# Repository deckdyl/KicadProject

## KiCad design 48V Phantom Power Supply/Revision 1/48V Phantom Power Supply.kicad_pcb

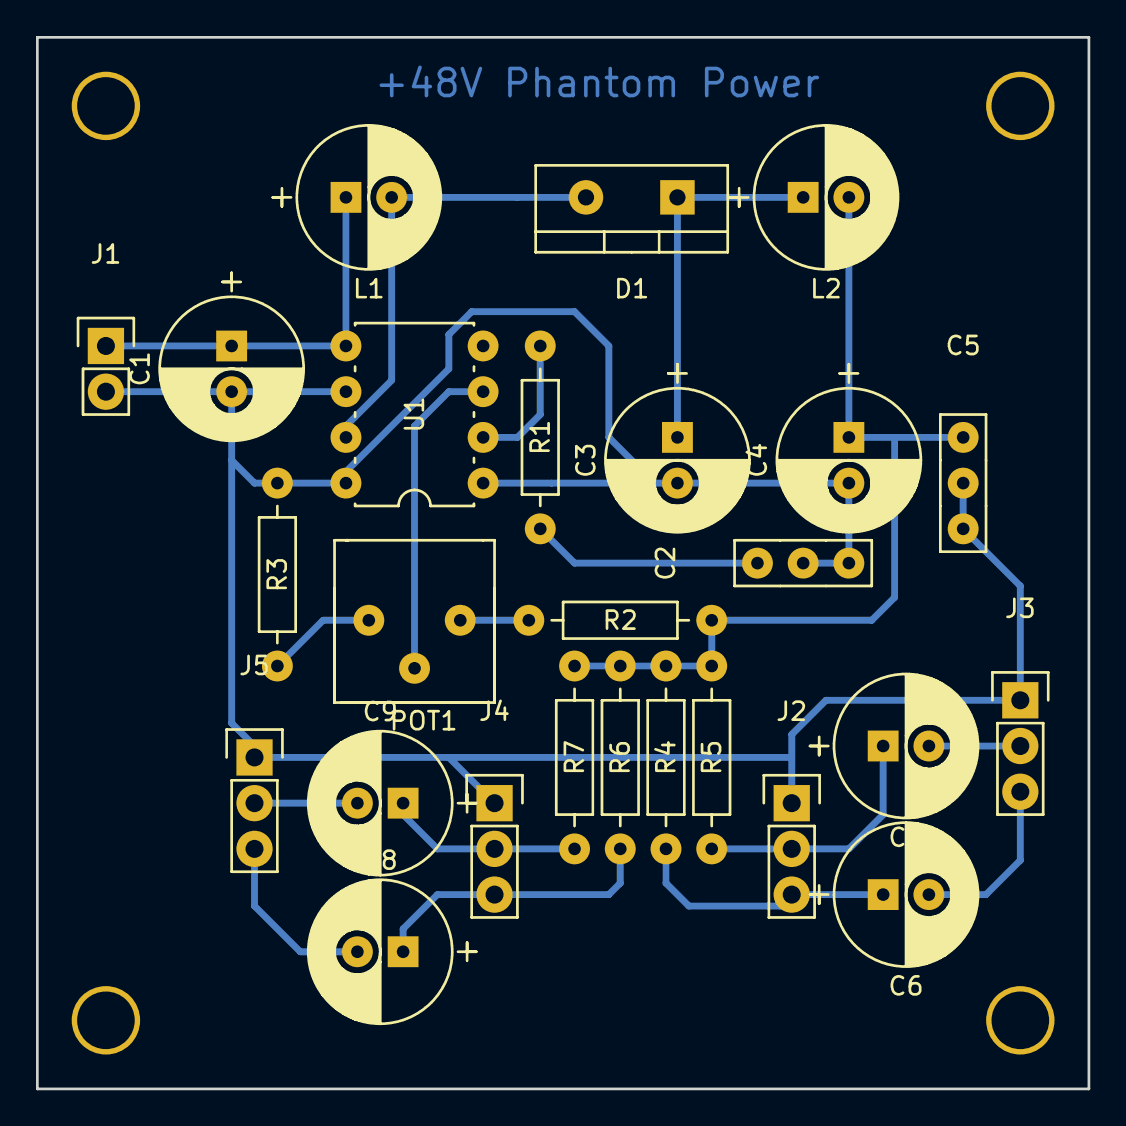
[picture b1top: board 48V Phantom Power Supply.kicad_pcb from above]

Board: 2 copper layers, 58.4 x 58.4 mm, 26 parts (0 on the bottom side), 18 nets.

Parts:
C1: 100uF; Cap_Pol_Radial_D8_P2
C2, C5: 100nF; Cap_UnPol_P3
C3, C4, C6, C7, C8, C9: 47uF; Cap_Pol_Radial_D8_P2
D1: MBR790; TO-220_Neutral12_Vertical
J1: Input; Pin_Header_Straight_1x02
J2: Mic_A_In; Pin_Header_Straight_1x03
J3: Mic_A_Out; Pin_Header_Straight_1x03
J4: Mic_B_In; Pin_Header_Straight_1x03
J5: Mic_B_Out; Pin_Header_Straight_1x03
L1, L2: 47uH; Cap_Pol_Radial_D8_P2
POT1: 500Ω; Potentiometer_Bourns_3386
R1: 1.2kΩ; Resistor-0.25W
R2: 47kΩ; Resistor-0.25W
R3: 820Ω; Resistor-0.25W
R4, R5, R6, R7: 6.8kΩ 1%; Resistor-0.25W
U1: LT1172; IC_PDIP_8pin

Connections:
+48V: C4.1, C5.1, L2.2, R2.1, R4.1, R5.1, R6.1, R7.1
Feedback: POT1.2, U1.3
GND: C1.2, C2.2, C3.2, C4.2, C5.2, J1.2, J2.1, J3.1, J4.1, J5.1, R3.2, U1.1, U1.6, U1.8
unnamed: C1.1, J1.1, L1.1, U1.5
unnamed: C2.1, R1.2
unnamed: C3.1, D1.1, L2.1
unnamed: C6.1, J2.3, R4.2
unnamed: C6.2, J3.3
unnamed: C7.1, J2.2, R5.2
unnamed: C7.2, J3.2
unnamed: C8.1, J4.3, R6.2
unnamed: C8.2, J5.3
unnamed: C9.1, J4.2, R7.2
unnamed: C9.2, J5.2
unnamed: D1.2, L1.2, U1.7
unnamed: POT1.1, R2.2
unnamed: POT1.3, R3.1
unnamed: R1.1, U1.2

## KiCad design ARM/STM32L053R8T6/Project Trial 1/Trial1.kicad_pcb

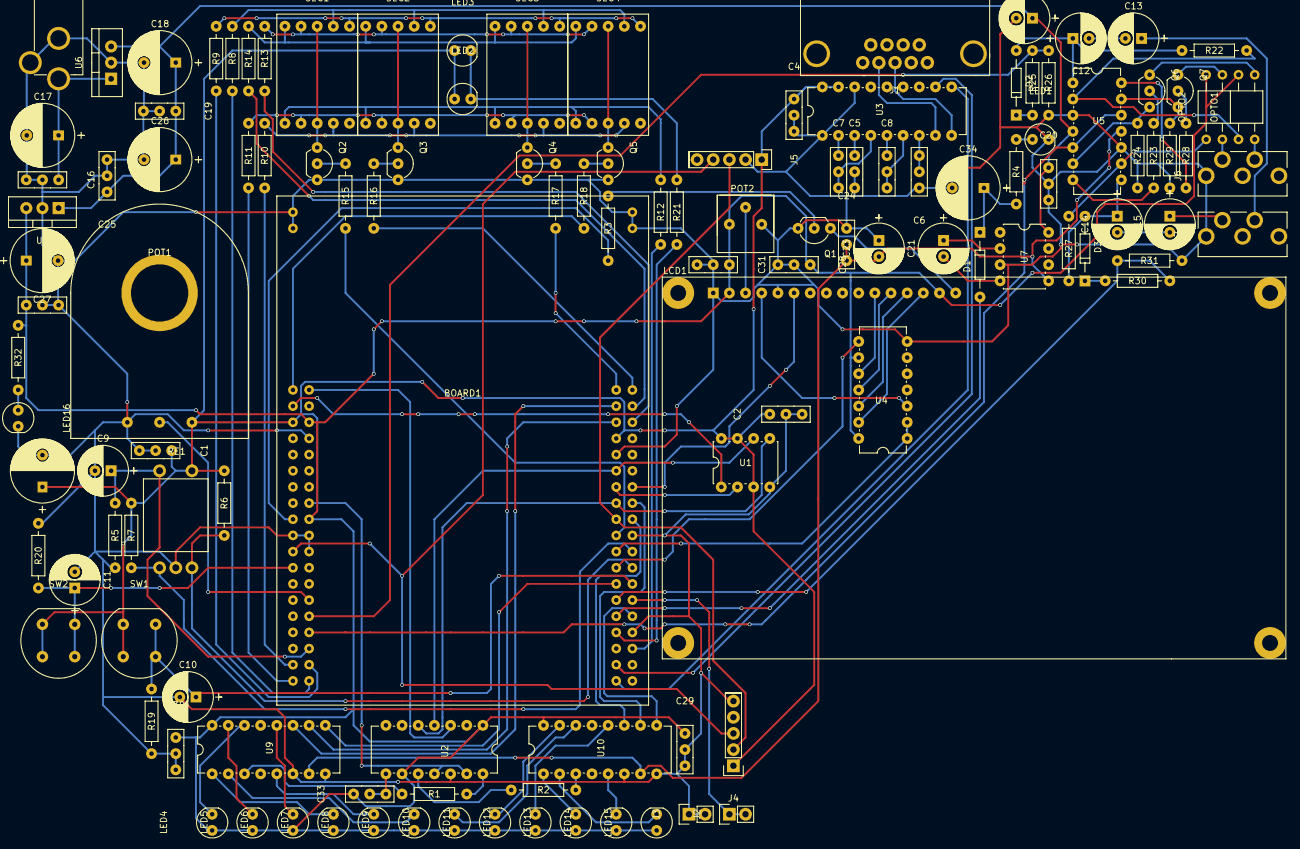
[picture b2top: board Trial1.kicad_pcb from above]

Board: 2 copper layers, 123 parts (0 on the bottom side), 121 nets.

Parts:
BOARD1: STM32L053R8T6_Nucleo
C1, C2, C4, C5, C6, C7, C8, C16, C19, C20, C24, C25, C28, C29, C30, C31, C32, C33: 100nF; Cap_UnPol_P3
C3, C17, C18, C26, C27, C34: 100uF; Cap_Pol_Radial_D10_P3
C9, C10, C11, C21, C22, C23: 10uF; Cap_Pol_Radial_D8_P2
C12, C13, C14, C15: 47uF; Cap_Pol_Radial_D8_P2
D1, D2, D3: 1N914; 1N4148
J1: DB9; RS232_DB9_Female_PCB_Mount
J2: RTC_CALIB; Pin_Header_Straight_1x02
J3: GND; Pin_Header_Straight_1x02
J4: BH1750; Pin_Header_Straight_1x05
J5: HMC5883L; Pin_Header_Straight_1x05
J6: AUDIO_IN; Audio_3.5mm_Socket
J7: AUDIO_OUT; Audio_3.5mm_Socket
J8: POWER; Power_Socket_2.1mm
LCD1: LCD2004; LCD_2004
LED1, LED2, LED3: LED_R; LED_5mm
LED4, LED5, LED6, LED7, LED8, LED9, LED10, LED11, LED12, LED13, LED14, LED15: LED_B; LED_5mm
LED16: LED_G; LED_5mm
OPTO1, OPTO2: NSL-32; NSL32
POT1: 1kΩ; Potentiometer_Large
POT2: 10kΩ; Potentiometer_Bourns_3386
Q1, Q2, Q3, Q4, Q5, Q6, Q7: 2N3904; TO-92_Inline_Wide
R1, R2: 270Ω; Resistor-0.25W
R3, R15, R16, R17, R18: 3.3kΩ; Resistor-0.25W
R4: 180Ω; Resistor-0.25W
R5, R6, R7, R19, R20, R22, R26, R27, R31: 10kΩ; Resistor-0.25W
R8, R9, R10, R11, R12, R13, R14, R21, R24, R29: 150Ω; Resistor-0.25W
R23, R28: 100Ω; Resistor-0.25W
R25, R30: 18kΩ; Resistor-0.25W
R32: 390Ω; Resistor-0.25W
RE1: Rotary_Encoder
SEG1, SEG2, SEG3, SEG4: 7Segment_CC; 7Seg_small
SW1, SW2: SW_PUSH; Round_Button
U1: 25LC256; IC_PDIP_8pin
U2: MCP4922; IC_PDIP_14pin
U3: SP3232ECP-L; IC_PDIP_18pin
U4: 74LS164; IC_PDIP_14pin
U5: LM324; IC_PDIP_14pin
U6: LM7809; TO-220_Neutral123_Vertical
U7: TC962; IC_PDIP_8pin
U8: LM7805; TO-220_Neutral123_Vertical
U9, U10: CD4051; IC_PDIP_16pin

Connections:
+3V3: BOARD1.+3V3, BOARD1.AREF, C1.1, C2.1, C3.1, C4.1, J4.1, J5.1, LED2.2, LED3.2, POT1.3, R6.1, R7.1, RE1.1, SW1.1, SW2.1, U1.3, U1.7, U1.8, U2.11, U2.13, U3.17, U3.18
+5V: BOARD1.+5V, BOARD1.E5V, C27.1, C28.1, C29.1, C30.1, C31.1, C32.1, C33.1, LCD1.2, LCD1.15, LED4.2, LED5.2, LED6.2, LED7.2, LED8.2, LED9.2, LED10.2, LED11.2, LED12.2, LED13.2, LED14.2, LED15.2, OPTO1.1, OPTO2.1, POT2.1, R32.1, U2.1, U2.9, U4.9, U4.14, U8.3, U9.16, U10.16
+9V: C18.1, C19.1, C20.1, C22.1, C25.1, C26.1, U5.4, U6.3, U7.8, U8.1
-9V: C23.2, C24.2, U5.11, U7.5, U9.7, U10.7
ADC_Input: BOARD1.PA0, POT1.2
AMUX_1A: BOARD1.PB8, U9.11
AMUX_1B: BOARD1.PB9, U9.10
AMUX_1C: BOARD1.PB10, U9.9
AMUX_2A: BOARD1.PB11, U10.11
AMUX_2B: BOARD1.PB12, U10.10
AMUX_2C: BOARD1.PB13, U10.9
AUDIO_IN_CH2: J6.2, OPTO2.4
AUDIO_OUT_CH2: C15.1, J7.2
AUDIO_PEAK_LED: BOARD1.PB5, D1.2
COMP1_INP: BOARD1.PA1, R25.2, R26.1
COMP2_INP: BOARD1.PB4, R30.2, R31.1
DAC_OUT1: BOARD1.PA4, U5.5, U5.12
FACTORY_RESET: BOARD1.PB15, C10.1, R19.1, SW1.2
GND: BOARD1.AGND, BOARD1.CN11, BOARD1.CN12, BOARD1.GND, C1.2, C2.2, C3.2, C4.2, C5.2, C6.1, C9.2, C10.2, C11.2, C16.2, C17.2, C18.2, C19.2, C20.2, C22.2, C23.1, C24.1, C25.2, C26.2, C27.2, C28.2, C29.2, C30.2, C31.2, C32.2, C33.2, C34.2, J3.1, J3.2, J4.5, J5.2, J6.3, J7.3, J8.2, J8.3, LCD1.1, LCD1.5, LED1.1, LED16.1, POT1.1, POT2.3, Q1.3, Q2.3, Q3.3, Q4.3, Q5.3, R5.2, R19.2, R20.2, R24.2, R26.2, R29.2, R31.2, RE1.4, U1.4, U2.8, U2.12, U3.1, U3.16, U4.7, U5.3, U5.10, U6.2, U7.3, U8.2, U9.6, U9.8, U10.6, U10.8
I2C_SCL: BOARD1.PB6, J4.2, J5.3
I2C_SDA: BOARD1.PB7, J4.3, J5.4
LCD_EN: BOARD1.PA11, LCD1.6
LCD_PWM_Out: BOARD1.PA15, R3.1
LED_COLON: BOARD1.PB3, R21.2
MCP4922_OUTA: R1.2, U9.3
MCP4922_OUTB: R2.2, U10.3
unnamed: BOARD1.PC0, R8.1
unnamed: BOARD1.PC1, R9.1
unnamed: BOARD1.PC2, R10.1
unnamed: BOARD1.PC3, R11.1
unnamed: BOARD1.PC4, R12.1
unnamed: BOARD1.PC5, R13.1
unnamed: BOARD1.PC6, R14.1
unnamed: C5.1, U3.3
unnamed: C6.2, U3.7
unnamed: C7.1, U3.2
unnamed: C7.2, U3.4
unnamed: C8.1, U3.5
unnamed: C8.2, U3.6
unnamed: C12.1, D2.2, R22.2, U5.1
unnamed: C12.2, C13.2
unnamed: C13.1, J7.1
unnamed: C14.1, D3.2, R27.2, U5.8
unnamed: C14.2, C15.2
unnamed: C16.1, C17.1, J8.1, U6.1
unnamed: C21.1, U7.2
unnamed: C21.2, U7.4
unnamed: C34.1, D1.1, R4.1
unnamed: D2.1, R25.1
unnamed: D3.1, R30.1
unnamed: J1.2, U3.8
unnamed: J1.3, U3.9
unnamed: J6.1, OPTO1.4
unnamed: LCD1.3, POT2.2
unnamed: LCD1.4, U4.3
unnamed: LCD1.11, U4.10
unnamed: LCD1.12, U4.11
unnamed: LCD1.13, U4.12
unnamed: LCD1.14, U4.13
unnamed: LCD1.16, Q1.1
unnamed: LED1.2, R4.2
unnamed: LED2.1, LED3.1, R21.1
unnamed: LED4.1, U9.14
unnamed: LED5.1, U9.15
unnamed: LED6.1, U9.12
unnamed: LED7.1, U9.1
unnamed: LED8.1, U9.5
unnamed: LED9.1, U9.2
unnamed: LED10.1, U10.14
unnamed: LED11.1, U10.15
unnamed: LED12.1, U10.12
unnamed: LED13.1, U10.1
unnamed: LED14.1, U10.5
unnamed: LED15.1, U10.2
unnamed: LED16.2, R32.2
unnamed: OPTO1.2, Q6.1
unnamed: OPTO1.3, R22.1, U5.2
unnamed: OPTO2.2, Q7.1
unnamed: OPTO2.3, R27.1, U5.9
unnamed: Q1.2, R3.2
unnamed: Q2.1, SEG1.3,8
unnamed: Q2.2, R15.2
unnamed: Q3.1, SEG2.3,8
unnamed: Q3.2, R16.2
unnamed: Q4.1, SEG3.3,8
unnamed: Q4.2, R17.2
unnamed: Q5.1, SEG4.3,8
unnamed: Q5.2, R18.2
unnamed: Q6.2, R23.2
unnamed: Q6.3, R24.1, U5.6
unnamed: Q7.2, R28.2
unnamed: Q7.3, R29.1, U5.13
unnamed: R1.1, U2.14
unnamed: R2.1, U2.10
unnamed: R8.2, SEG1.7, SEG2.7, SEG3.7, SEG4.7
unnamed: R9.2, SEG1.6, SEG2.6, SEG3.6, SEG4.6
unnamed: R10.2, SEG1.4, SEG2.4, SEG3.4, SEG4.4
unnamed: R11.2, SEG1.2, SEG2.2, SEG3.2, SEG4.2
unnamed: R12.2, SEG1.1, SEG2.1, SEG3.1, SEG4.1
unnamed: R13.2, SEG1.9, SEG2.9, SEG3.9, SEG4.9
unnamed: R14.2, SEG1.10, SEG2.10, SEG3.10, SEG4.10
unnamed: R23.1, U5.7
unnamed: R28.1, U5.14
RE_OUT1: BOARD1.PB1, R6.2, RE1.3
RE_OUT2: BOARD1.PB2, R7.2, RE1.5
RE_SW: BOARD1.PB0, C9.1, R5.1, RE1.2
RTC_OUT_CALIB: BOARD1.PB14, J2.1, J2.2
RTC_Timestamp: BOARD1.PC13, C11.1, R20.1, SW2.2
SEG1: BOARD1.PC7, R15.1
SEG2: BOARD1.PC8, R16.1
SEG3: BOARD1.PC9, R17.1
SEG4: BOARD1.PC10, R18.1
SPI_MISO: BOARD1.PA6, U1.2
SPI_MOSI: BOARD1.PA7, U1.5, U2.5
SPI_SCK: BOARD1.PA5, U1.6, U2.4
SPI_SS_DAC: BOARD1.PC11, U2.3
SPI_SS_EEPROM: BOARD1.PC12, U1.1
USART1_SYNC_CK: BOARD1.PA8, U4.8
USART1_SYNC_TX: BOARD1.PA9, U4.1, U4.2
USART2_RX: BOARD1.PA3, U3.10
USART2_TX: BOARD1.PA2, U3.11

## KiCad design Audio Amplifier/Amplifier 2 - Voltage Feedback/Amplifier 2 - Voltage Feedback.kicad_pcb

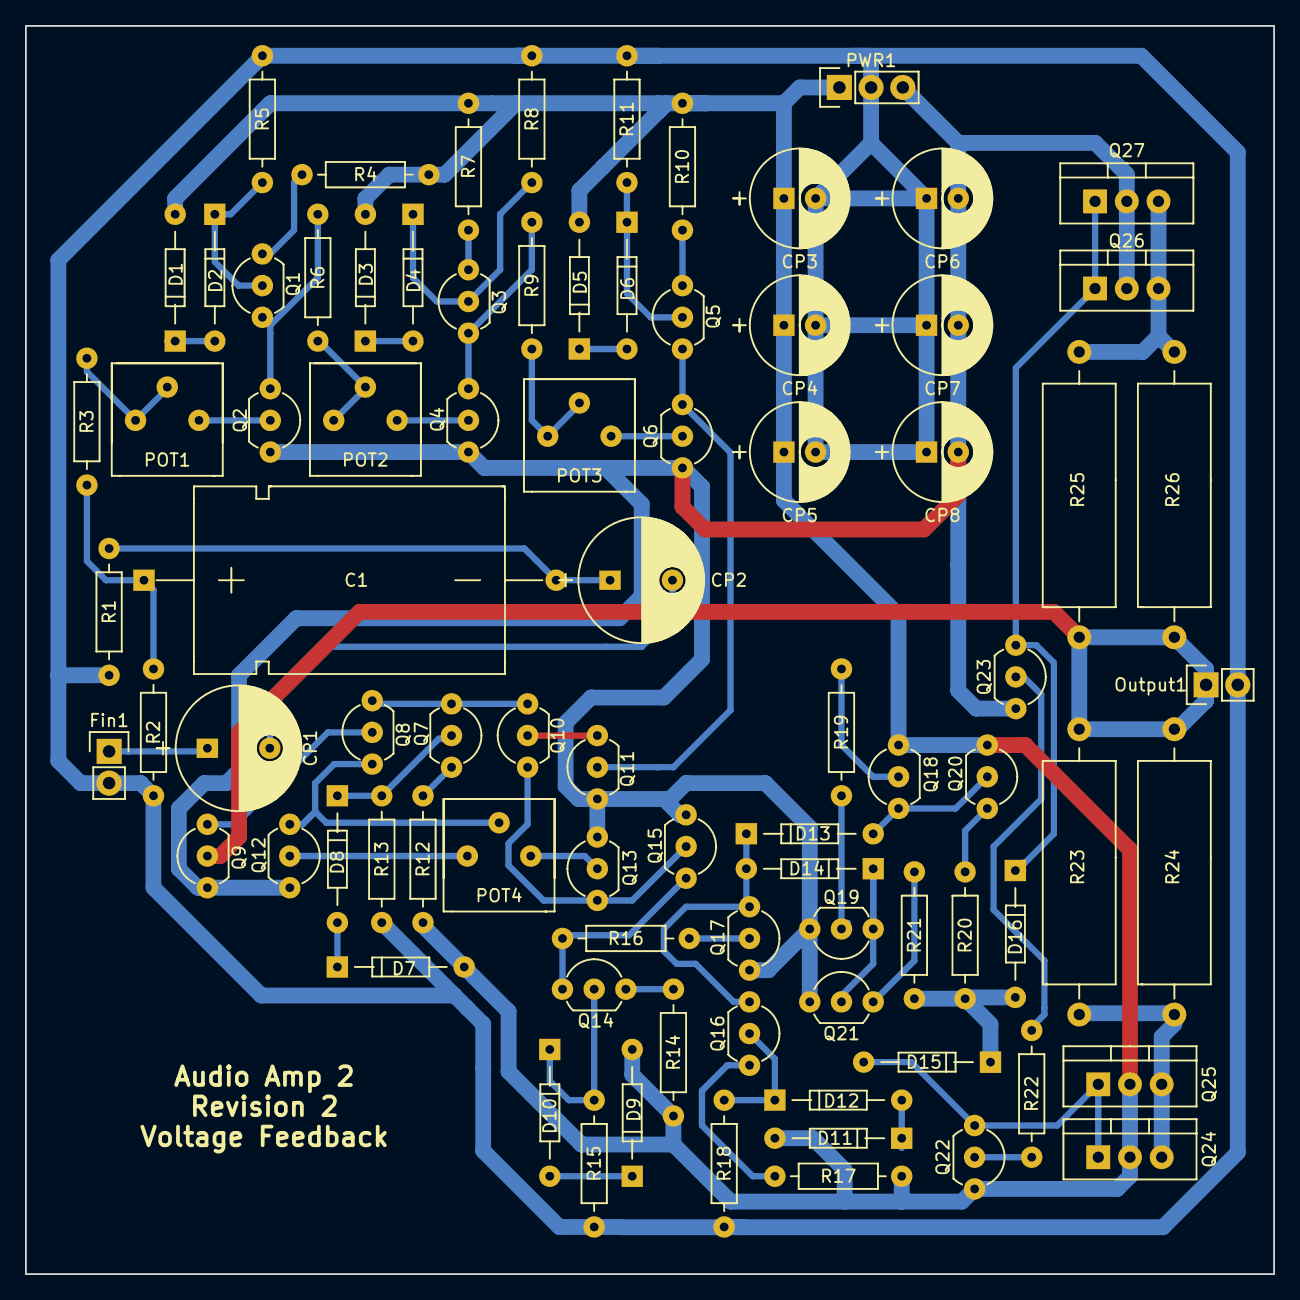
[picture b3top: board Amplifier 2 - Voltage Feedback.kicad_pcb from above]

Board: 2 copper layers, 100.0 x 100.0 mm, 85 parts (0 on the bottom side), 58 nets.

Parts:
C1: 33uF; Cap_Pol_Axial_D13_L26_P14
CP1, CP2: 470uF; Cap_Pol_Radial_D10_P3
CP3, CP4, CP5, CP6, CP7, CP8: 100uF; Cap_Pol_Radial_D8_P2
D1, D2, D3, D4, D5, D6, D7, D8, D9, D10, D11, D12, D13, D14, D15, D16: 1N4148
Fin1: CONN_01X02; Pin_Header_Straight_1x02
Output1: CONN_01X02; Pin_Header_Straight_1x02
POT1, POT2, POT3: 5kΩ; Potentiometer_Bourns_3386
POT4: 20Ω; Potentiometer_Bourns_3386
PWR1: CONN_01X03; Pin_Header_Straight_1x03
Q1, Q3, Q5, Q7, Q8, Q9, Q10, Q11, Q14, Q15, Q16, Q18, Q21, Q22: 2N3906; TO-92_Inline_Wide
Q2, Q4, Q6, Q12, Q13, Q17, Q19, Q20, Q23: 2N3904; TO-92_Inline_Wide
Q24, Q25: TIP31; TO-220_Neutral123_Vertical
Q26, Q27: TIP32; TO-220_Neutral123_Vertical
R1, R2: 470Ω; Resistor-0.25W
R3, R6, R9: 28kΩ; Resistor-0.25W
R4, R7, R10, R12: 5Ω; Resistor-0.25W
R5, R8, R11, R13, R15, R18: 10kΩ; Resistor-0.25W
R14: 4.7KΩ; Resistor-0.25W
R16: 330Ω; Resistor-0.25W
R17: 75Ω; Resistor-0.25W
R19: 1MΩ; Resistor-0.25W
R20, R21: 1Ω; Resistor-0.25W
R22: 47kΩ; Resistor-0.25W
R23, R24, R25, R26: 3Ω3 2W; Resistor-2W

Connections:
+15V: CP3.1, CP4.1, CP5.1, D1.2, D3.2, D5.2, D7.2, D9.2, D11.2, PWR1.1, Q18.3, Q20.1, Q22.3, Q24.2, Q25.2, R4.1, R7.1, R10.1, R12.1, R14.1, R17.1
-15V: CP6.2, CP7.2, CP8.2, PWR1.3, Q2.3, Q4.3, Q6.3, Q9.1, Q11.1, Q12.3, Q13.3, Q15.1, Q17.3, Q19.3, Q21.1, Q23.3, Q26.2, Q27.2
Fampin: Q5.1, Q6.1, Q11.2
Fampout: D15.1, D16.2, R20.2, R21.1
GND: CP3.2, CP4.2, CP5.2, CP6.1, CP7.1, CP8.1, Fin1.2, Output1.2, PWR1.2, R1.2, R2.2, R5.2, R8.2, R11.2, R13.2, R15.2, R18.2
unnamed: C1.1, R2.1, R3.2
unnamed: C1.2, CP2.1, R1.1
unnamed: CP1.1, Fin1.1
unnamed: CP1.2, CP2.2
unnamed: D1.1, D2.2
unnamed: D2.1, Q1.2, R5.1
unnamed: D3.1, D4.2
unnamed: D4.1, Q3.2, R8.1
unnamed: D5.1, D6.2
unnamed: D6.1, Q5.2, R11.1
unnamed: D7.1, D8.2
unnamed: D8.1, Q7.2, R13.1
unnamed: D10.1, Q14.2, R15.1
unnamed: D9.1, D10.2
unnamed: D11.1, D12.2
unnamed: D12.1, Q16.2, R18.1
unnamed: D13.1, D14.2, Q16.1, Q17.1
unnamed: D13.2, Q18.1, Q20.2
unnamed: D14.1, Q19.1, Q21.2
unnamed: D15.2, Q22.1, Q24.1, Q25.1
unnamed: D16.1, Q23.1, Q26.1, Q27.1
unnamed: POT1.1, POT1.2, R3.1
unnamed: POT1.3, Q2.2
unnamed: POT2.1, POT2.2, R6.1
unnamed: POT2.3, Q4.2
unnamed: POT3.1, POT3.2, R9.1
unnamed: POT3.3, Q6.2
unnamed: POT4.1, Q12.2
unnamed: POT4.2, Q8.1, Q12.1
unnamed: POT4.3, Q13.2
unnamed: Q1.1, Q2.1, R6.2
unnamed: Q1.3, R4.2
unnamed: Q3.1, Q4.1, R9.2
unnamed: Q3.3, R7.2
unnamed: Q5.3, R10.2
unnamed: Q7.3, R12.2
unnamed: Q8.2, Q9.3
unnamed: Q10.1, Q13.1, Q15.2
unnamed: Q10.2, Q11.3
unnamed: Q7.1, Q8.3, Q10.3
unnamed: Q14.1, Q15.3, R16.1
unnamed: Q14.3, R14.2
unnamed: Q16.3, R17.2
unnamed: Q17.2, R16.2
unnamed: Q18.2, R19.1
unnamed: Q19.2, R19.2
unnamed: Q20.3, R20.1
unnamed: Q21.3, R21.2
unnamed: Q22.2, R22.1
unnamed: Q23.2, R22.2
unnamed: Q24.3, Q25.3, R23.1, R24.1
unnamed: Q26.3, Q27.3, R25.2, R26.2
Output: Output1.1, Q9.2, R23.2, R24.2, R25.1, R26.1

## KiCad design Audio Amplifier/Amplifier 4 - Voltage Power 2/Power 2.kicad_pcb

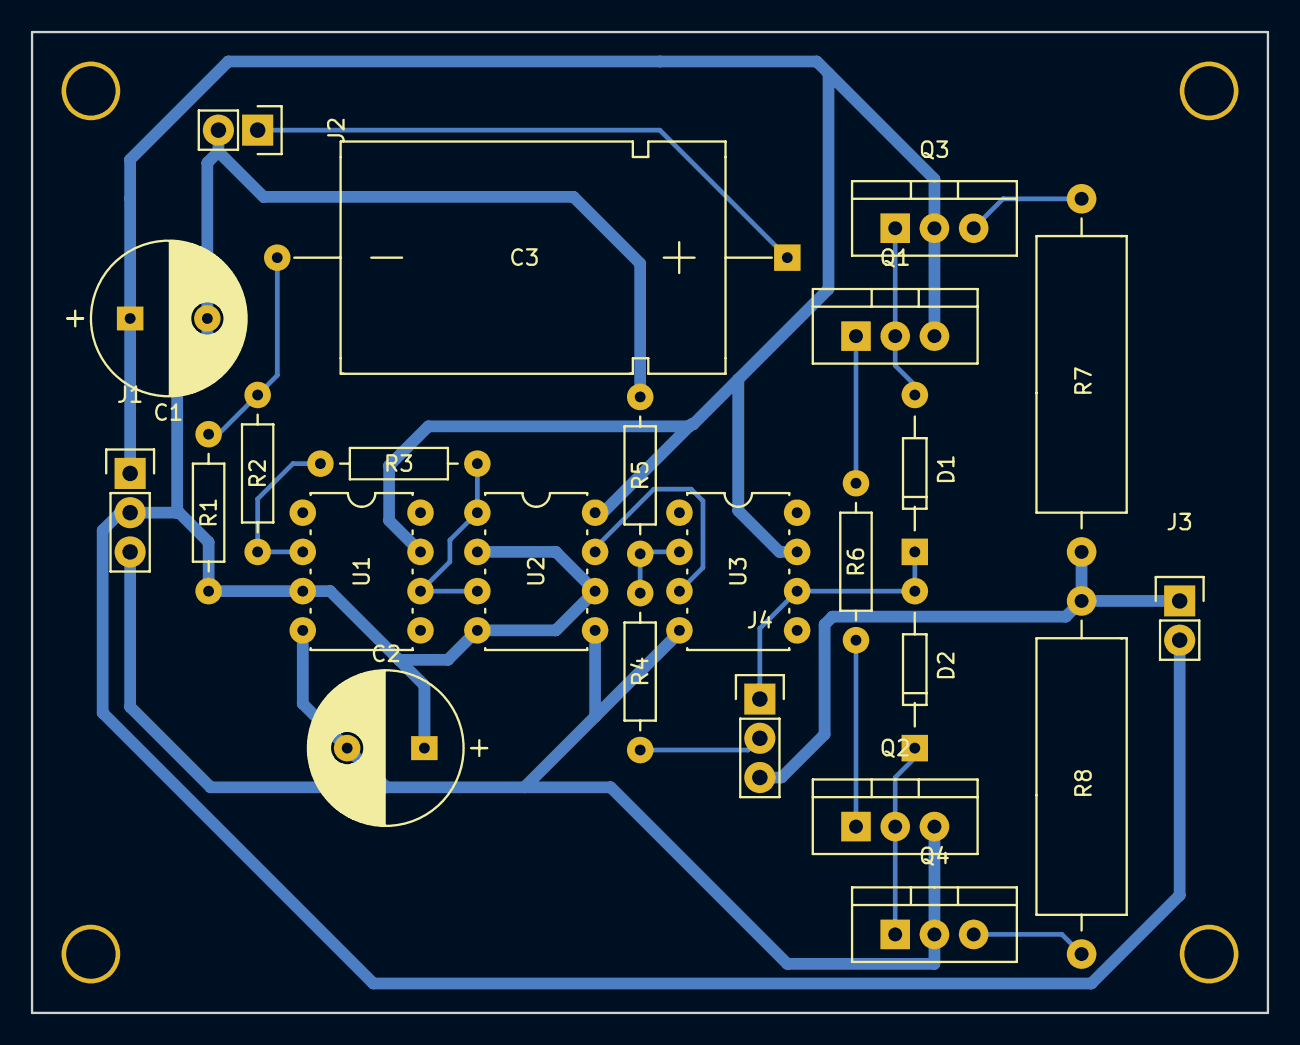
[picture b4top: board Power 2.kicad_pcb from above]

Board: 2 copper layers, 80.0 x 63.5 mm, 24 parts (0 on the bottom side), 18 nets.

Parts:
C1, C2: 100uF; Cap_Pol_Radial_D10_P3
C3: 33uF; Cap_Pol_Axial_D13_L26_P14
D1, D2: 1N4148
J1: PWR; Pin_Header_Straight_1x03
J2: Fin; Pin_Header_Straight_1x02
J3: Speaker Output; Pin_Header_Straight_1x02
J4: selector; Pin_Header_Straight_1x03
Q1, Q4: TIP32; TO-220_Neutral123_Vertical
Q2, Q3: TIP31; TO-220_Neutral123_Vertical
R1: 470Ω; Resistor-0.25W
R2: 10kΩ; Resistor-0.25W
R3: 33kΩ; Resistor-0.25W
R4: 100kΩ; Resistor-0.25W
R5: 10KΩ; Resistor-0.25W
R6: 65kΩ; Resistor-0.25W
R7, R8: 3.3Ω; Resistor-2W
U1, U3: OPA552; IC_PDIP_8pin
U2: AD633; IC_PDIP_8pin

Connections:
+15V: C1.1, J1.1, Q1.3, Q3.2, U1.7, U2.8, U3.7
-15V: C2.2, J1.3, Q2.3, Q4.2, U1.4, U2.5, U3.4
GND: C1.2, C2.1, J1.2, J2.2, J3.2, R1.1, R5.1, U1.3, U2.2, U2.4, U2.6
unnamed: C3.1, J2.1
unnamed: C3.2, R1.2, R2.2
unnamed: D1.1, D2.2, J4.1, U3.6
unnamed: D1.2, Q1.2, Q3.1
unnamed: D2.1, Q2.2, Q4.1
unnamed: J3.1, J4.3, R7.2, R8.1
unnamed: J4.2, R4.2
unnamed: Q1.1, R6.1
unnamed: Q2.1, R6.2
unnamed: Q3.3, R7.1
unnamed: Q4.3, R8.2
unnamed: R2.1, R3.2, U1.2
unnamed: R3.1, U1.6, U2.1, U2.3
unnamed: R4.1, R5.2, U3.2
unnamed: U2.7, U3.3

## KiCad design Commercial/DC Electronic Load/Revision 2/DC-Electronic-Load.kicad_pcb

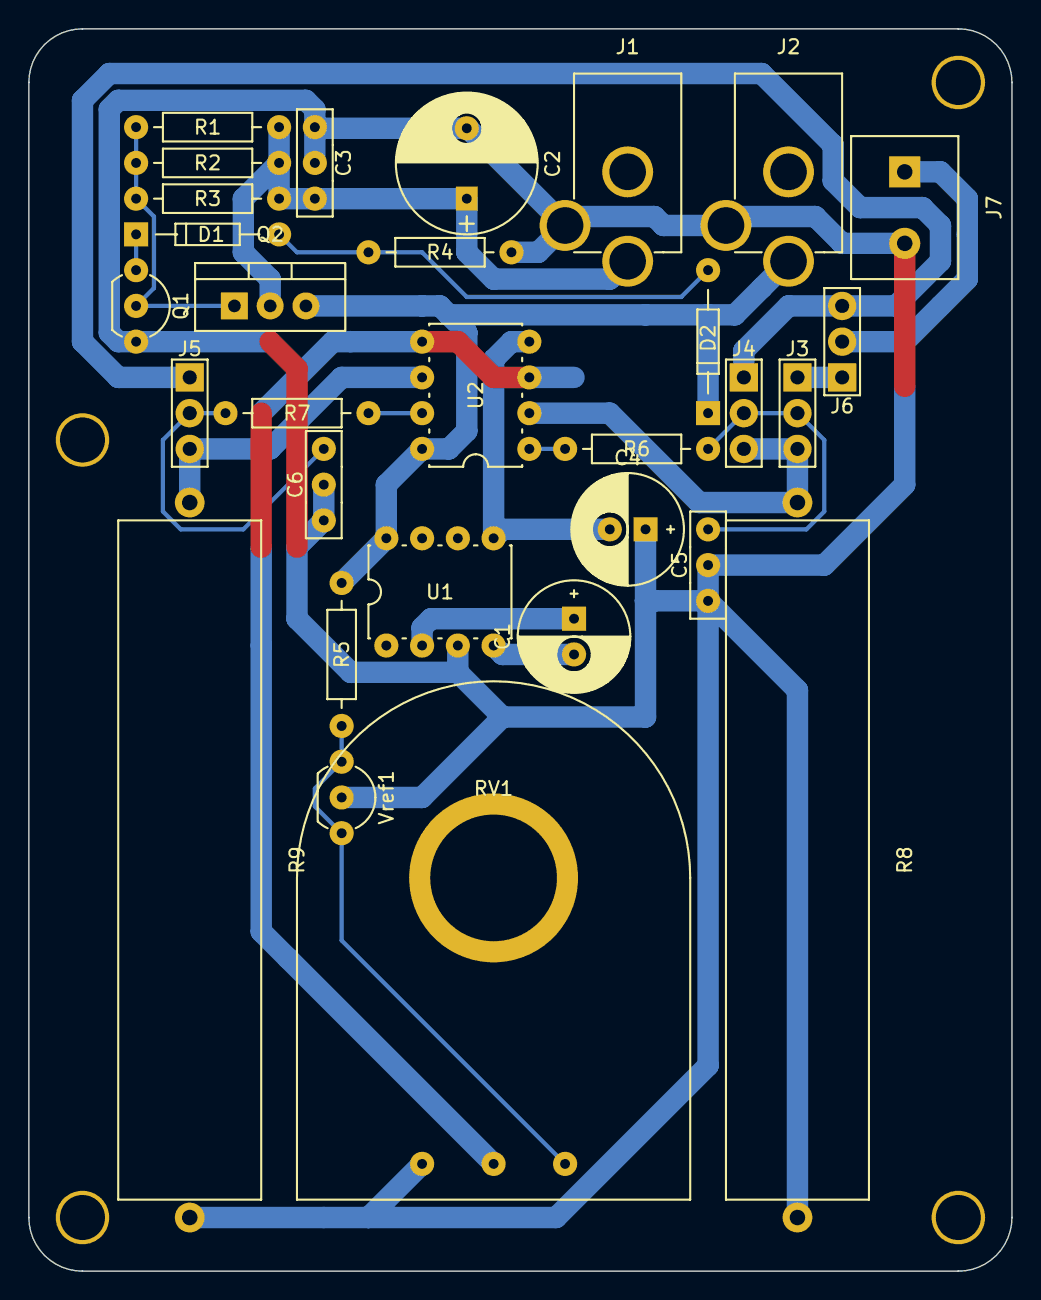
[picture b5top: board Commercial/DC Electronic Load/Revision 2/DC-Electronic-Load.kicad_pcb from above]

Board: 2 copper layers, 69.8 x 88.3 mm, 30 parts (0 on the bottom side), 20 nets.

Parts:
C1, C4: 22uF; Cap_Pol_Radial_D8_P2
C2: 100uF; Cap_Pol_Radial_D10_P3
C3, C5, C6: 100nF; Cap_UnPol_P3
D1: 1N4148
D2: 11V; 1N4148
J1: Power; Power_Socket_2.1mm
J2: Fan; Power_Socket_2.1mm
J3, J4, J5: MOSFET; Pin_Header_Straight_1x03
J6: Switch; Pin_Header_Straight_1x03
J7: PSU_IN; Terminal_Block-5mm
Q1: 2N3904; TO-92_Inline_Wide
Q2: TIP112; TO-220_Neutral123_Vertical
R1, R2, R3: 120Ω; Resistor-0.25W
R4: 100kΩ; Resistor-0.25W
R5: 2.2kΩ; Resistor-0.25W
R6, R7: 100Ω; Resistor-0.25W
R8, R9: 0.1Ω; Resistor-10W
RV1: 50kΩ; Potentiometer_Large
U1: TC962; IC_PDIP_8pin
U2: LM358; IC_PDIP_8pin
Vref1: TL431; TO-92_Inline_Wide

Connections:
+12V: D2.1, J2.1, Q2.3, R5.1, U1.8, U2.8
-12V: C4.2, U1.5, U2.4
GND: C2.2, C3.2, C4.1, C5.2, C6.2, J1.2, J2.2, J7.2, Q1.3, R4.2, R8.2, R9.2, RV1.1, U1.3, Vref1.2
unnamed: C1.1, U1.2
unnamed: C1.2, U1.4
unnamed: C2.1, C3.1, J1.1, Q2.2, R1.1, R2.1, R3.1
unnamed: C5.1, J3.2, J4.2, R6.1
unnamed: C6.1, J5.2, R7.1
unnamed: D1.1, Q1.1
unnamed: D1.2, D2.2, R4.1
unnamed: J3.1, J6.1
unnamed: J3.3, J4.3, R8.1, U2.2
unnamed: J4.1, J5.1, J6.3
unnamed: J5.3, R9.1, U2.6
unnamed: J6.2, J7.1
unnamed: Q1.2, Q2.1, R1.2, R2.2, R3.2
unnamed: R5.2, RV1.3, Vref1.1, Vref1.3
unnamed: R6.2, U2.1
unnamed: R7.2, U2.7
unnamed: RV1.2, U2.3, U2.5
